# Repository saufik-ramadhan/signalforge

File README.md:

# signalforge
Swiss Army for Hackers

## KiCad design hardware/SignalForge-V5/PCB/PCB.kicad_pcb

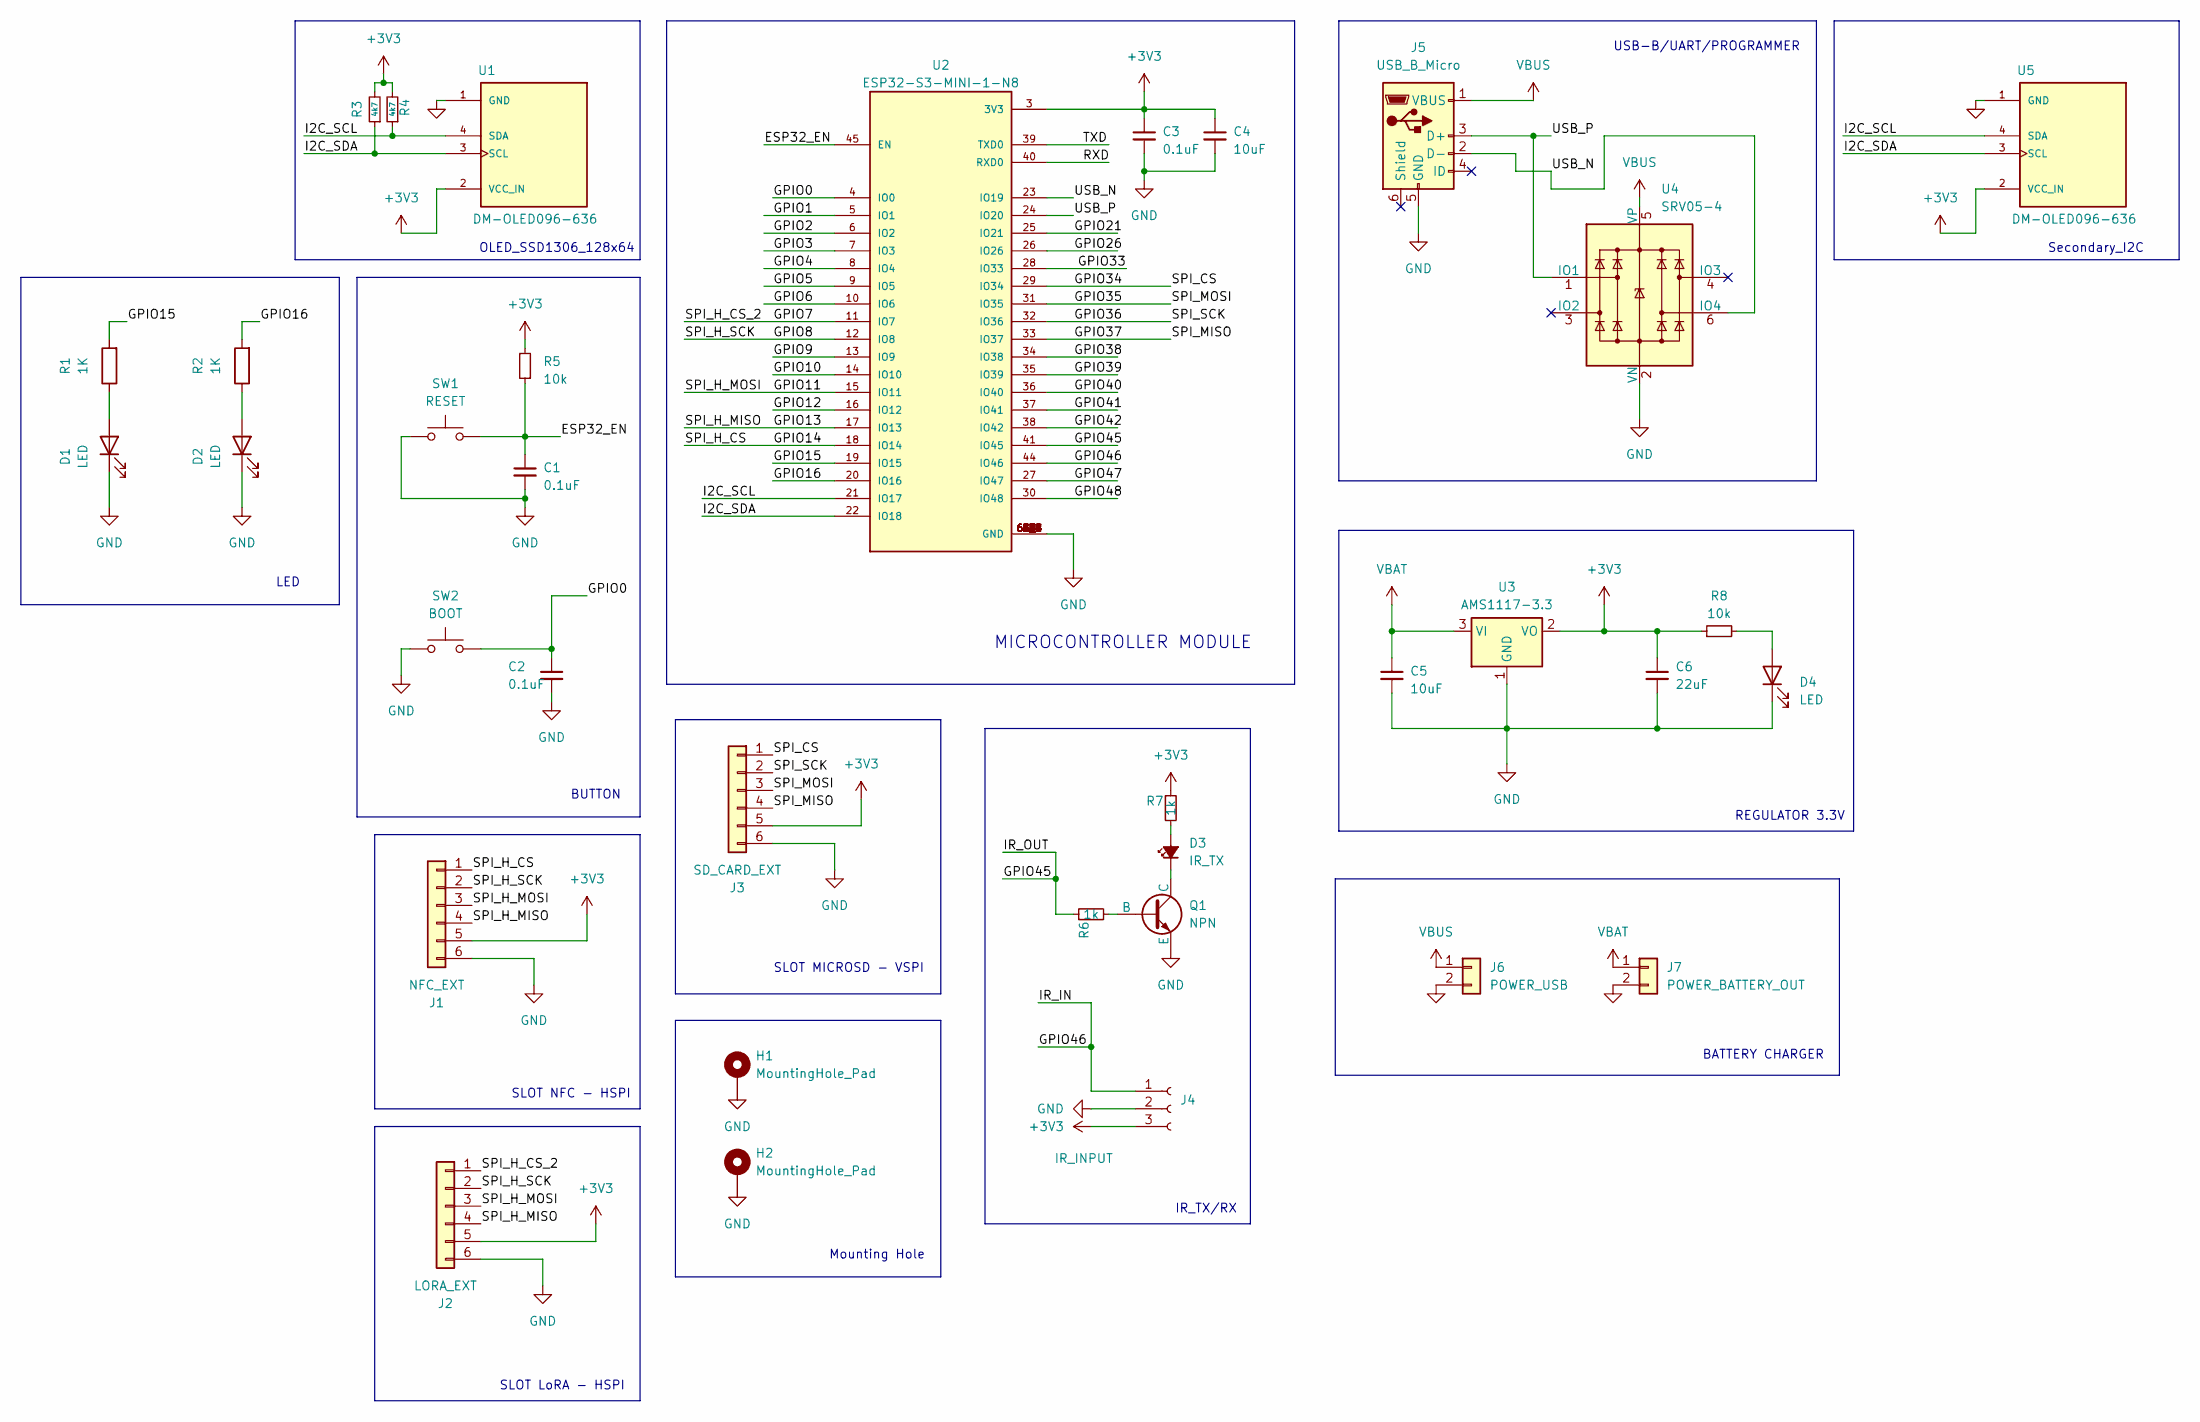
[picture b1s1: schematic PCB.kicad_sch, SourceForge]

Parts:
C1, C2, C3: 0.1uF; C_0603_1608Metric
C4, C5: 10uF; C_0603_1608Metric
C6: 22uF; C_0603_1608Metric
D1, D2, D4: LED; LED_0603_1608Metric
D3: IR_TX; PinSocket_1x02_P2.54mm_Vertical
H1, H2: MountingHole_Pad; MountingHole_3.2mm_M3_DIN965_Pad
J1: NFC_EXT; PinSocket_1x06_P2.54mm_Vertical
J2: LORA_EXT; PinSocket_1x06_P2.54mm_Vertical
J3: SD_CARD_EXT; PinSocket_1x06_P2.54mm_Vertical
J4: IR_INPUT; PinSocket_1x03_P2.54mm_Vertical
J5: USB_B_Micro; PinSocket_1x05_P2.54mm_Vertical
J6: POWER_USB; PinSocket_1x02_P2.54mm_Vertical
J7: POWER_BATTERY_OUT; PinSocket_1x02_P2.54mm_Vertical
Q1: NPN; SOT-23_Handsoldering
R1, R2: 1K; R_0603_1608Metric
R3, R4: 4k7; R_0603_1608Metric
R5, R8: 10k; R_0603_1608Metric
R6, R7: 1k; R_0603_1608Metric
SW1: RESET; SW_Push_1P1T_NO_CK_KSC6xxJ
SW2: BOOT; SW_Push_1P1T_NO_CK_KSC6xxJ
U1, U5: DM-OLED096-636; PinSocket_1x04_P2.54mm_Vertical; PARTREV 2018-09-10
U2: ESP32-S3-MINI-1-N8; XCVR_ESP32-S3-MINI-1-N8; PARTREV v0.6
U3: AMS1117-3.3; SOT-223-3_TabPin2
U4: SRV05-4; SOT-23-6

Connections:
+3V3: C3.1, C4.1, C6.1, J1.5, J2.5, J3.5, J4.3, R3.2, R4.2, R5.2, R7.1, R8.1, U1.2 (VCC_IN), U2.3 (3V3), U3.2 (VO), U5.2 (VCC_IN)
/ESP32_EN: C1.1, R5.1, SW1.2, U2.45 (EN)
/GPIO0: C2.1, SW2.2, U2.4 (IO0)
/GPIO1: U2.5 (IO1)
/GPIO2: U2.6 (IO2)
/GPIO3: U2.7 (IO3)
/GPIO4: U2.8 (IO4)
/GPIO5: U2.9 (IO5)
/GPIO6: U2.10 (IO6)
/GPIO7: J2.1, U2.11 (IO7)
/GPIO8: J1.2, J2.2, U2.12 (IO8)
/GPIO9: U2.13 (IO9)
/GPIO10: U2.14 (IO10)
/GPIO11: J1.3, J2.3, U2.15 (IO11)
/GPIO12: U2.16 (IO12)
/GPIO13: J1.4, J2.4, U2.17 (IO13)
/GPIO14: J1.1, U2.18 (IO14)
/GPIO15: R1.2, U2.19 (IO15)
/GPIO16: R2.2, U2.20 (IO16)
/GPIO21: U2.25 (IO21)
/GPIO26: U2.26 (IO26)
/GPIO33: U2.28 (IO33)
/GPIO34: J3.1, U2.29 (IO34)
/GPIO35: J3.3, U2.31 (IO35)
/GPIO36: J3.2, U2.32 (IO36)
/GPIO37: J3.4, U2.33 (IO37)
/GPIO38: U2.34 (IO38)
/GPIO39: U2.35 (IO39)
/GPIO40: U2.36 (IO40)
/GPIO41: U2.37 (IO41)
/GPIO42: U2.38 (IO42)
/GPIO45: R6.1, U2.41 (IO45)
/GPIO46: J4.1, U2.44 (IO46)
/GPIO47: U2.27 (IO47)
/GPIO48: U2.30 (IO48)
/I2C_SCL: R4.1, U1.4 (SDA), U2.21 (IO17), U5.4 (SDA)
/I2C_SDA: R3.1, U1.3 (SCL), U2.22 (IO18), U5.3 (SCL)
/RXD: U2.40 (RXD0)
/TXD: U2.39 (TXD0)
/USB_N: J5.2 (D-), U2.23 (IO19), U4.6 (IO4)
/USB_P: J5.3 (D+), U2.24 (IO20), U4.1 (IO1)
GND: C1.2, C2.2, C3.2, C4.2, C5.2, C6.2, D1.1 (K), D2.1 (K), D4.1 (K), H1.1, H2.1, J1.6, J2.6, J3.6, J4.2, J5.5 (GND), J6.2, J7.2, Q1.3 (E), SW1.1, SW2.1, U1.1 (GND), U2.1 (GND), U2.2 (GND), U2.42 (GND), U2.43 (GND), U2.46 (GND), U2.47 (GND), U2.48 (GND), U2.49 (GND), U2.50 (GND), U2.51 (GND), U2.52 (GND), U2.53 (GND), U2.54 (GND), U2.55 (GND), U2.56 (GND), U2.57 (GND), U2.58 (GND), U2.59 (GND), U2.60 (GND), U2.61 (GND), U2.61_1 (GND), U2.61_2 (GND), U2.61_3 (GND), U2.61_4 (GND), U2.61_5 (GND), U2.61_6 (GND), U2.61_7 (GND), U2.61_8 (GND), U2.62 (GND), U2.63 (GND), U2.64 (GND), U2.65 (GND), U3.1 (GND), U4.2 (VN), U5.1 (GND)
unnamed: D1.2 (A), R1.1
unnamed: D2.2 (A), R2.1
unnamed: D3.2 (A), R7.2
unnamed: D3.1 (K), Q1.1 (C)
unnamed: D4.2 (A), R8.2
unnamed: Q1.2 (B), R6.2
VBAT: C5.1, J7.1, U3.3 (VI)
VBUS: J5.1 (VBUS), J6.1, U4.5 (VP)

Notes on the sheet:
USB-B/UART/PROGRAMMER
OLED_SSD1306_128x64
Mounting Hole
LED
SLOT NFC - HSPI
REGULATOR 3.3V
SLOT LoRA - HSPI
Secondary_I2C
BATTERY CHARGER
BUTTON
MICROCONTROLLER MODULE
IR_TX/RX
SLOT MICROSD - VSPI

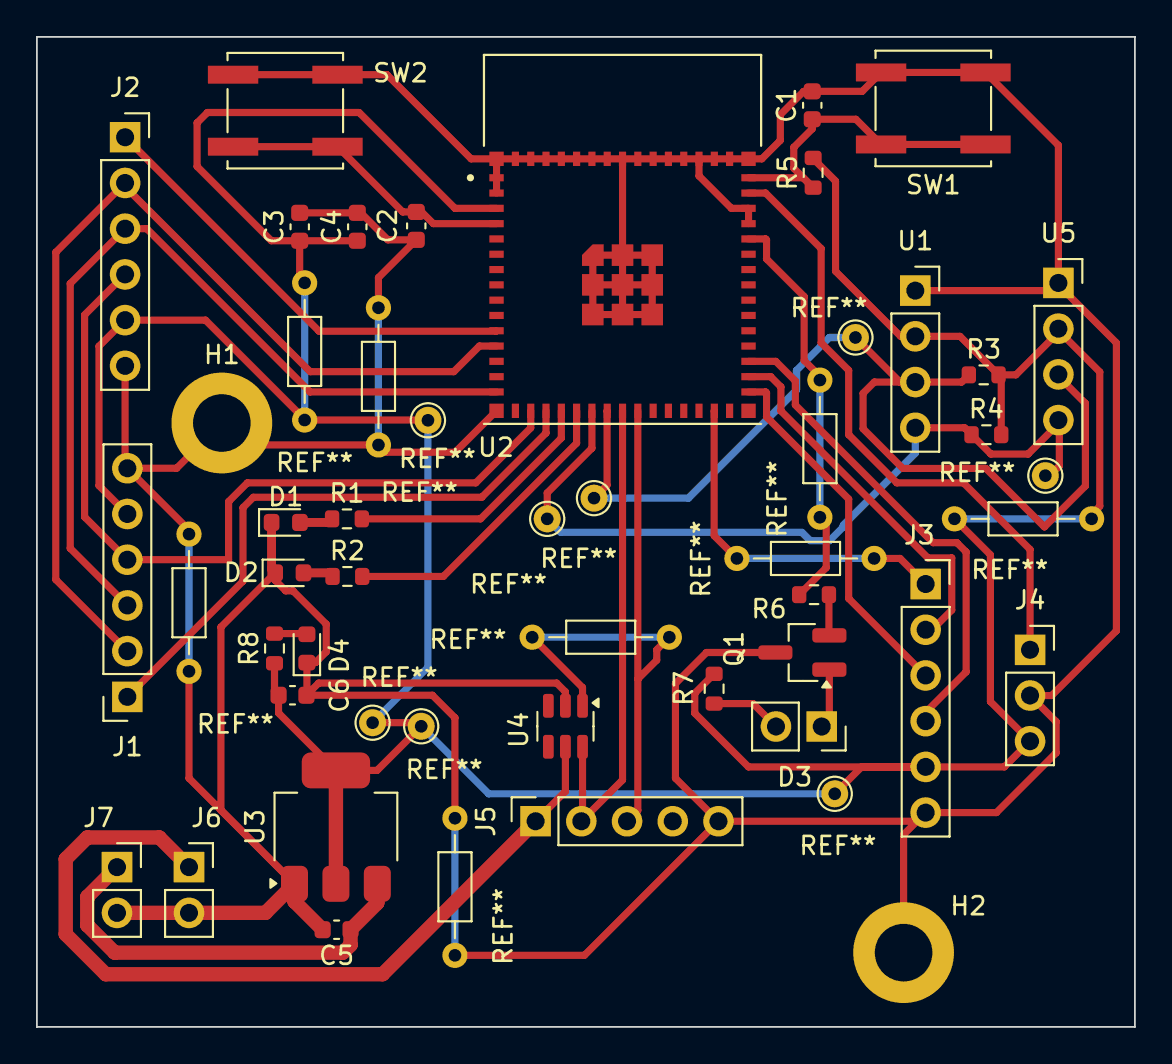
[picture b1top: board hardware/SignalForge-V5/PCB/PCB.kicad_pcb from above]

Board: 2 copper layers, 61.0 x 55.0 mm, 35 parts (0 on the bottom side), 29 nets.

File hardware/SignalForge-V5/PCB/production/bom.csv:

Designator,Footprint,Quantity,Value,LCSC Part #
"C1, C2, C3",0603,3,0.1uF,
"C4, C5",0603,2,10uF,
C6,0603,1,22uF,
"D1, D2, D4",0603,3,LED,
D3,PinSocket_1x02_P2.54mm_Vertical,1,IR_TX,
J1,PinSocket_1x06_P2.54mm_Vertical,1,NFC_EXT,
J2,PinSocket_1x06_P2.54mm_Vertical,1,LORA_EXT,
J3,PinSocket_1x06_P2.54mm_Vertical,1,SD_CARD_EXT,
J4,PinSocket_1x03_P2.54mm_Vertical,1,IR_INPUT,
J5,PinSocket_1x05_P2.54mm_Vertical,1,USB_B_Micro,
J6,PinSocket_1x02_P2.54mm_Vertical,1,POWER_USB,
J7,PinSocket_1x02_P2.54mm_Vertical,1,POWER_BATTERY_OUT,
Q1,SOT-23_Handsoldering,1,NPN,
"R1, R2, R6, R7",0603,4,1K,
"R3, R4",0603,2,4k7,
"R5, R8",0603,2,10k,
SW1,SW_Push_1P1T_NO_CK_KSC6xxJ,1,RESET,
SW2,SW_Push_1P1T_NO_CK_KSC6xxJ,1,BOOT,
"U1, U5",PinSocket_1x04_P2.54mm_Vertical,2,DM-OLED096-636,
U2,XCVR_ESP32-S3-MINI-1-N8,1,ESP32-S3-MINI-1-N8,
U3,SOT-223-3_TabPin2,1,AMS1117-3.3,
U4,SOT-23-6,1,SRV05-4,

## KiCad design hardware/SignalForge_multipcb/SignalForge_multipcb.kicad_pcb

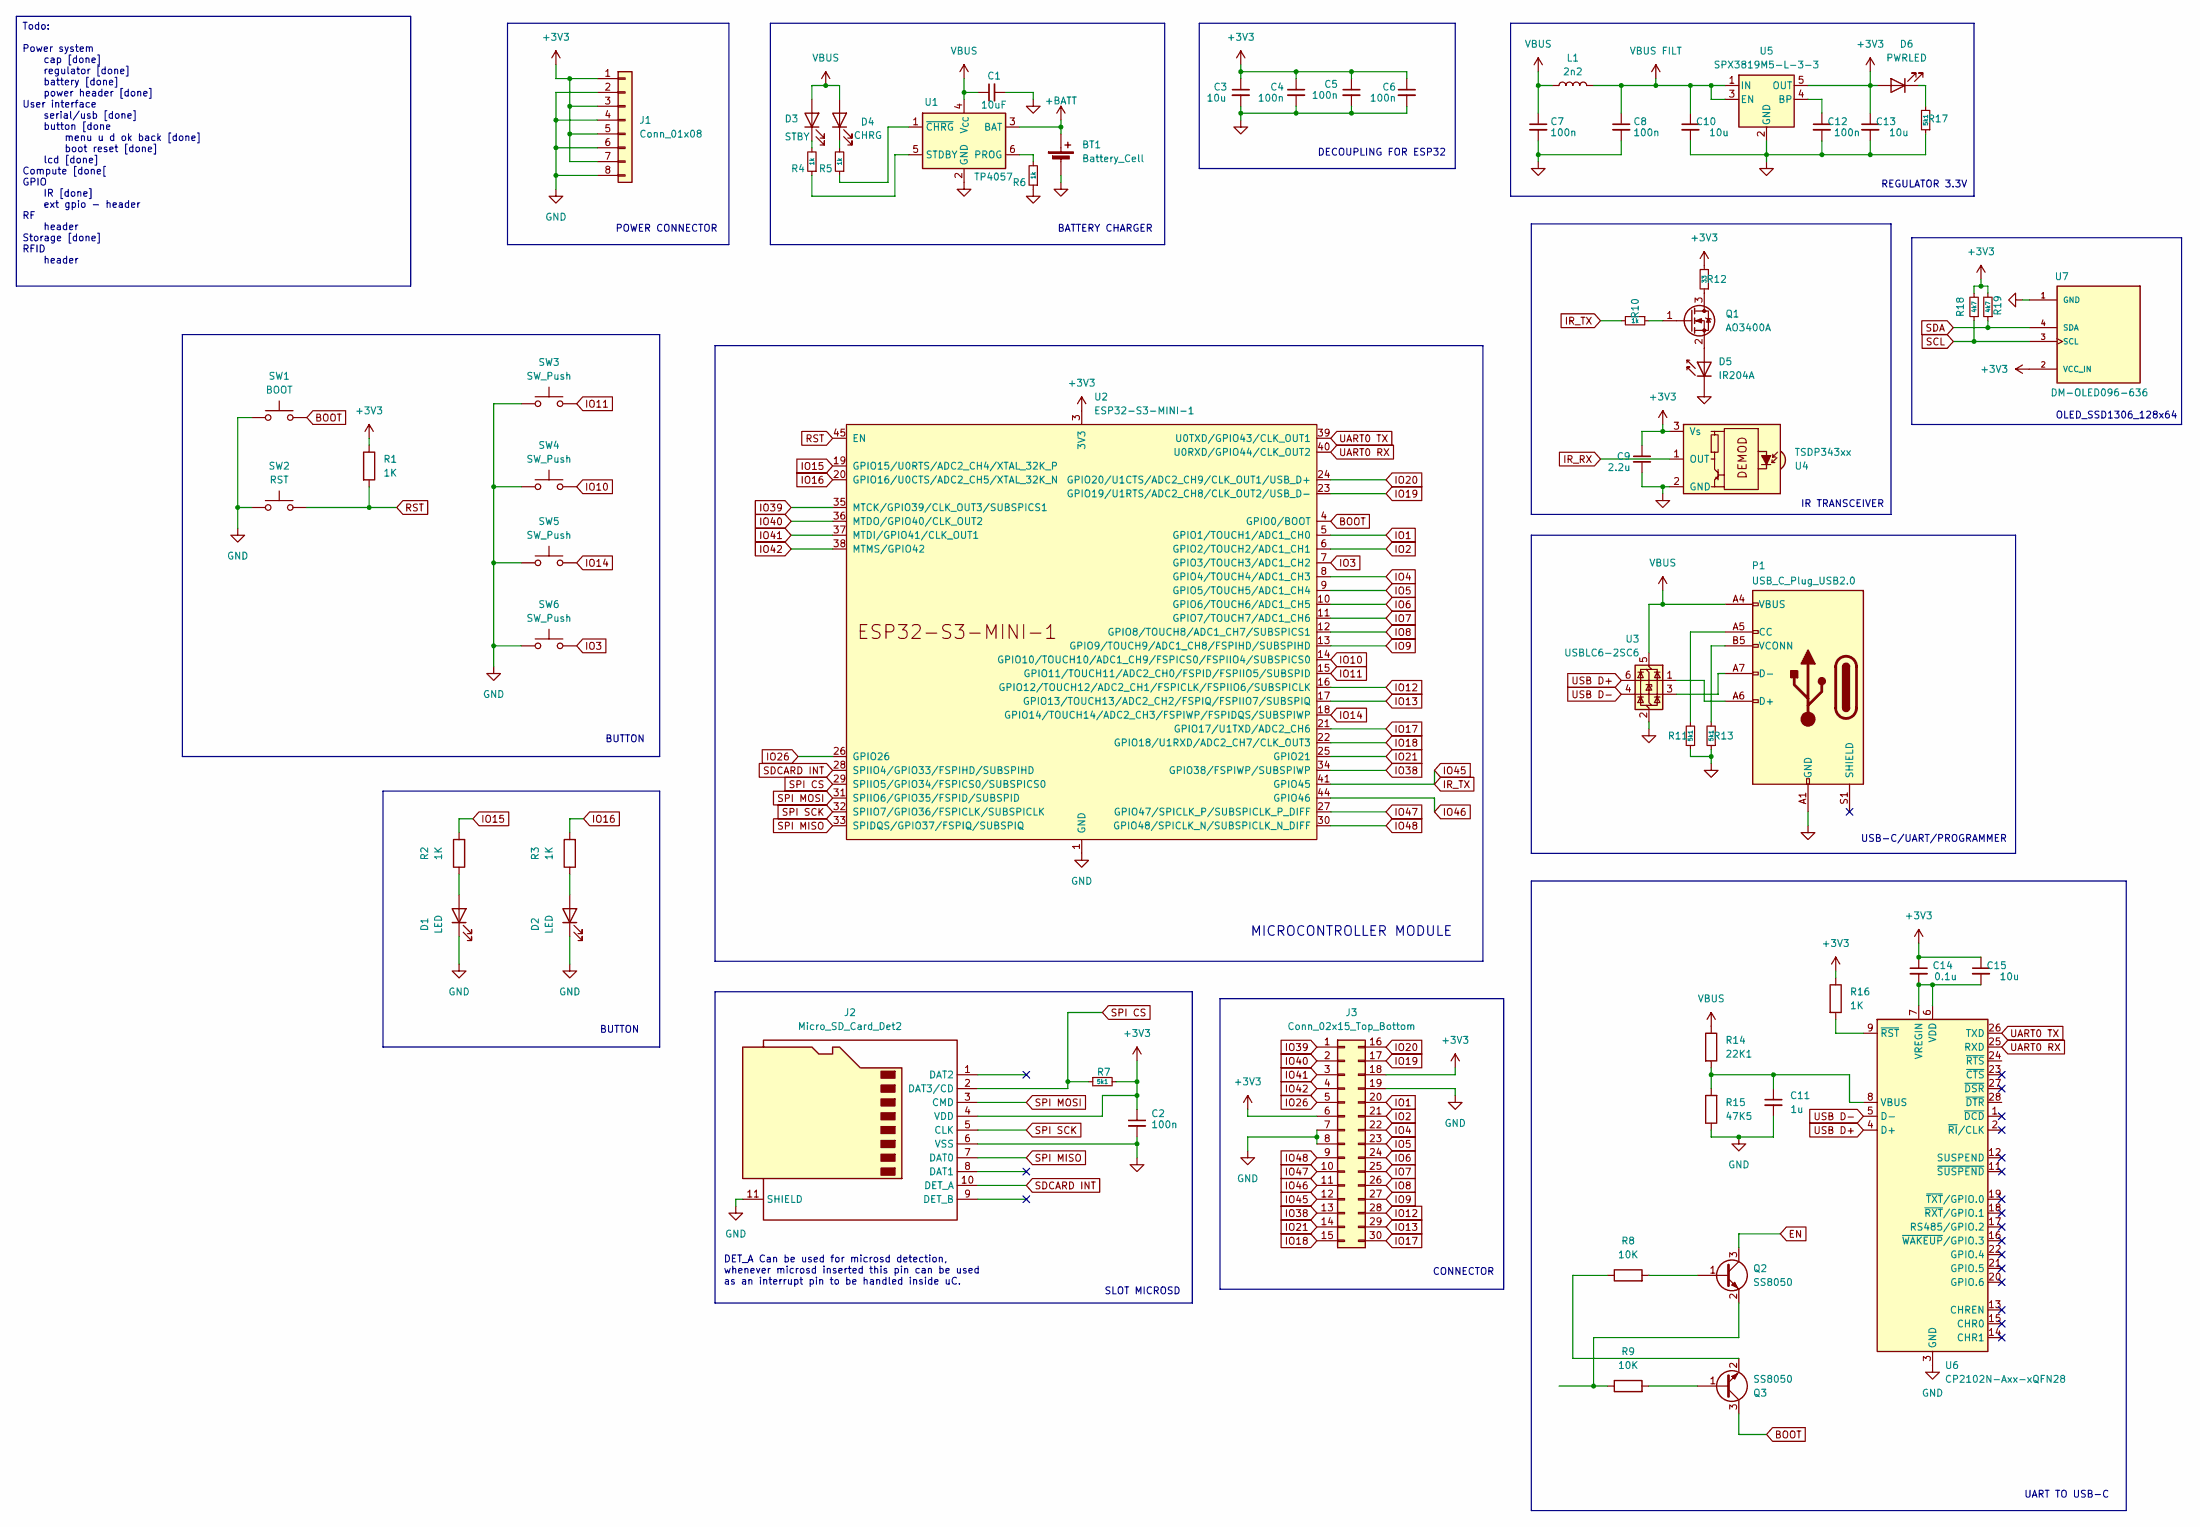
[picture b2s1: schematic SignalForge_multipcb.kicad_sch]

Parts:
BT1: Battery_Cell; SW_PUSH_6mm
C1: 10uF; C_0402_1005Metric
C2, C4, C5, C6, C7, C8, C12: 100n; C_0402_1005Metric
C3, C10, C13, C15: 10u; R_0402_1005Metric_Pad0.72x0.64mm_HandSolder
C9: 2.2u; C_0402_1005Metric
C11: 1u; C_0402_1005Metric
C14: 0.1u; C_0402_1005Metric
D1, D2: LED; LED_D3.0mm_IRBlack
D3: STBY; LED_D3.0mm_IRBlack
D4: CHRG; LED_D3.0mm_IRBlack
D5: IR204A; LED_D3.0mm_IRBlack
D6: PWRLED; LED_D3.0mm_IRBlack
J1: Conn_01x08; PinHeader_1x08_P2.54mm_Vertical
J2: Micro_SD_Card_Det2; microSD_HC_Hirose_DM3BT-DSF-PEJS
J3: Conn_02x15_Top_Bottom; PinHeader_2x15_P2.54mm_Vertical
L1: 2n2; L_0603_1608Metric
P1: USB_C_Plug_USB2.0; USB_C_Receptacle_GCT_USB4105-xx-A_16P_TopMnt_Horizontal
Q1: AO3400A; TO-247-3_Vertical
Q2, Q3: SS8050; TO-247-3_Vertical
R1, R2, R3, R16: 1K; R_1206_3216Metric
R4, R5, R6, R10: 1k; R_1206_3216Metric
R7, R11, R13, R17: 5k1; R_1206_3216Metric
R8, R9: 10K; R_1206_3216Metric
R12: 33; R_1206_3216Metric
R14: 22K1; R_1206_3216Metric
R15: 47K5; R_1206_3216Metric
R18, R19: 4k7; R_1206_3216Metric
SW1: BOOT; SW_SPST_Omron_B3FS-105xP
SW2: RST; SW_SPST_Omron_B3FS-105xP
SW3, SW4, SW5, SW6: SW_Push; SW_SPST_Omron_B3FS-105xP
U1: TP4057; TSOT-23-6
U2: ESP32-S3-MINI-1
U3: USBLC6-2SC6; SOT-23-6
U4: TSDP343xx; Vishay_MOLD-3Pin
U5: SPX3819M5-L-3-3; SOT-23-5
U6: CP2102N-Axx-xQFN28; QFN-28-1EP_5x5mm_P0.5mm_EP3.35x3.35mm
U7: DM-OLED096-636; PinSocket_1x04_P2.54mm_Vertical; PARTREV 2018-09-10

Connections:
+3V3: C2.1, C3.1, C4.1, C5.1, C6.1, C9.1, C13.1, C14.1, C15.1, D6.2 (A), J1.1, J1.3, J1.5, J1.7, J2.4 (VDD), J3.6, J3.18, R1.1, R7.2, R12.2, R16.1, R18.2, R19.2, U2.3 (3V3), U4.3 (Vs), U5.5 (OUT), U7.2 (VCC_IN)
+BATT: BT1.1 (+), U1.3 (BAT)
BOOT: Q3.3 (C), SW1.2, U2.4 (GPIO0/BOOT)
EN: Q2.3 (C)
GND: BT1.2 (-), C1.2, C2.2, C3.2, C4.2, C5.2, C6.2, C7.2, C8.2, C9.2, C10.2, C11.2, C12.2, C13.2, D1.1 (K), D2.1 (K), D5.1 (K), J1.2, J1.4, J1.6, J1.8, J2.6 (VSS), J2.11 (SHIELD), J3.7, J3.8, J3.19, P1.A1 (GND), P1.A12 (GND), P1.B1 (GND), P1.B12 (GND), R6.1, R11.1, R13.1, R15.1, R17.1, SW1.1, SW2.1, SW3.1, SW4.1, SW5.1, SW6.1, U1.2 (GND), U2.1 (GND), U2.2 (GND), U2.42 (GND), U2.43 (GND), U2.46 (GND), U2.47 (GND), U2.48 (GND), U2.49 (GND), U2.50 (GND), U2.51 (GND), U2.52 (GND), U2.53 (GND), U2.54 (GND), U2.55 (GND), U2.56 (GND), U2.57 (GND), U2.58 (GND), U2.59 (GND), U2.60 (GND), U2.61 (GND), U2.62 (GND), U2.63 (GND), U2.64 (GND), U2.65 (GND), U3.2 (GND), U4.2 (GND), U5.2 (GND), U6.3 (GND), U6.29 (GND), U7.1 (GND)
IO1: J3.20, U2.5 (GPIO1/TOUCH1/ADC1_CH0)
IO2: J3.21, U2.6 (GPIO2/TOUCH2/ADC1_CH1)
IO3: SW6.2, U2.7 (GPIO3/TOUCH3/ADC1_CH2)
IO4: J3.22, U2.8 (GPIO4/TOUCH4/ADC1_CH3)
IO5: J3.23, U2.9 (GPIO5/TOUCH5/ADC1_CH4)
IO6: J3.24, U2.10 (GPIO6/TOUCH6/ADC1_CH5)
IO7: J3.25, U2.11 (GPIO7/TOUCH7/ADC1_CH6)
IO8: J3.26, U2.12 (GPIO8/TOUCH8/ADC1_CH7/SUBSPICS1)
IO9: J3.27, U2.13 (GPIO9/TOUCH9/ADC1_CH8/FSPIHD/SUBSPIHD)
IO10: SW4.2, U2.14 (GPIO10/TOUCH10/ADC1_CH9/FSPICS0/FSPIIO4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)
IO11: SW3.2, U2.15 (GPIO11/TOUCH11/ADC2_CH0/FSPID/FSPIIO5/S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)
IO12: J3.28, U2.16 (GPIO12/TOUCH12/ADC2_CH1/FSPICLK/FSPIIO6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)
IO13: J3.29, U2.17 (GPIO13/TOUCH13/ADC2_CH2/FSPIQ/FSPIIO7/S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)
IO14: SW5.2, U2.18 (GPIO14/TOUCH14/ADC2_CH3/FSPIWP/FSPIDQS/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)
IO15: R2.2, U2.19 (GPIO15/U0RTS/ADC2_CH4/XTAL_32K_P)
IO16: R3.2, U2.20 (GPIO16/U0CTS/ADC2_CH5/XTAL_32K_N)
IO17: J3.30, U2.21 (GPIO17/U1TXD/ADC2_CH6)
IO18: J3.15, U2.22 (GPIO18/U1RXD/ADC2_CH7/CLK_OUT3)
IO19: J3.17, U2.23 (GPIO19/U1RTS/ADC2_CH8/CLK_OUT2/USB_D-)
IO20: J3.16, U2.24 (GPIO20/U1CTS/ADC2_CH9/CLK_OUT1/USB_D+)
IO21: J3.14, U2.25 (GPIO21)
IO26: J3.5, U2.26 (GPIO26)
IO38: J3.13, U2.34 (GPIO38/FSPIWP/SUBSPIWP)
IO39: J3.1, U2.35 (MTCK/GPIO39/CLK_OUT3/SUBSPICS1)
IO40: J3.2, U2.36 (MTDO/GPIO40/CLK_OUT2)
IO41: J3.3, U2.37 (MTDI/GPIO41/CLK_OUT1)
IO42: J3.4, U2.38 (MTMS/GPIO42)
IO45: J3.12, R10.2, U2.41 (GPIO45)
IO46: J3.11, U2.44 (GPIO46)
IO47: J3.10, U2.27 (GPIO47/SPICLK_P/SUBSPICLK_P_DIFF)
IO48: J3.9, U2.30 (GPIO48/SPICLK_N/SUBSPICLK_N_DIFF)
IR_RX: U4.1 (OUT)
unnamed: D1.2 (A), R2.1
unnamed: D2.2 (A), R3.1
unnamed: D3.1 (K), R4.2
unnamed: D4.1 (K), R5.2
unnamed: D5.2 (A), Q1.2 (S)
unnamed: D6.1 (K), R17.2
unnamed: P1.A5 (CC), R11.2
unnamed: P1.A6 (D+), U3.1 (I/O1)
unnamed: P1.A7 (D-), U3.3 (I/O2)
unnamed: P1.B5 (VCONN), R13.2
unnamed: Q1.3 (D), R12.1
unnamed: Q1.1 (G), R10.1
unnamed: Q2.1 (B), R8.2
unnamed: Q2.2 (E), R9.1
unnamed: Q3.1 (B), R9.2
unnamed: Q3.2 (E), R8.1
unnamed: R6.2, U1.6 (PROG)
unnamed: R4.1, U1.5 (STDBY)
unnamed: R5.1, U1.1 (~CHRG)
unnamed: C12.1, U5.4 (BP)
unnamed: C11.1, R14.2, R15.2, U6.8 (VBUS)
unnamed: C14.2, C15.2, U6.6 (VDD), U6.7 (VREGIN)
unnamed: R16.2, U6.9 (~RST)
RST: R1.2, SW2.2, U2.45 (EN)
SCL: R18.1, U7.3 (SCL)
SDA: R19.1, U7.4 (SDA)
SDCARD INT: J2.10 (DET_A), U2.28 (SPIIO4/GPIO33/FSPIHD/SUBSPIHD)
SPI CS: J2.2 (DAT3/CD), R7.1, U2.29 (SPIIO5/GPIO34/FSPICS0/SUBSPICS0)
SPI MISO: J2.7 (DAT0), U2.33 (SPIDQS/GPIO37/FSPIQ/SUBSPIQ)
SPI MOSI: J2.3 (CMD), U2.31 (SPIIO6/GPIO35/FSPID/SUBSPID)
SPI SCK: J2.5 (CLK), U2.32 (SPIIO7/GPIO36/FSPICLK/SUBSPICLK)
UART0 RX: U2.40 (U0RXD/GPIO44/CLK_OUT2), U6.25 (RXD)
UART0 TX: U2.39 (U0TXD/GPIO43/CLK_OUT1), U6.26 (TXD)
USB D+: U3.6 (I/O1), U6.4 (D+)
USB D-: U3.4 (I/O2), U6.5 (D-)
VBUS: C1.1, C7.1, D3.2 (A), D4.2 (A), L1.1, P1.A4 (VBUS), P1.A9 (VBUS), P1.B4 (VBUS), P1.B9 (VBUS), R14.1, U1.4 (V_{CC}), U3.5 (VBUS)
VBUS FILT: C8.1, C10.1, L1.2, U5.1 (IN), U5.3 (EN)

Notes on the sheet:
Todo: Power system cap [done] regulator [done] battery [done] power header [done] User interface serial/usb [done] button [done menu u d ok back [done] boot reset [done] lcd [done] Compute [done[ GPIO IR [done] ext gpio - header RF header Storage [done] RFID header
POWER CONNECTOR
IR TRANSCEIVER
USB-C/UART/PROGRAMMER
CONNECTOR
BUTTON
UART TO USB-C
MICROCONTROLLER MODULE
BATTERY CHARGER
OLED_SSD1306_128x64
DECOUPLING FOR ESP32
REGULATOR 3.3V
DET_A Can be used for microsd detection, whenever microsd inserted this pin can be used as an interrupt pin to be handled inside uC.
SLOT MICROSD

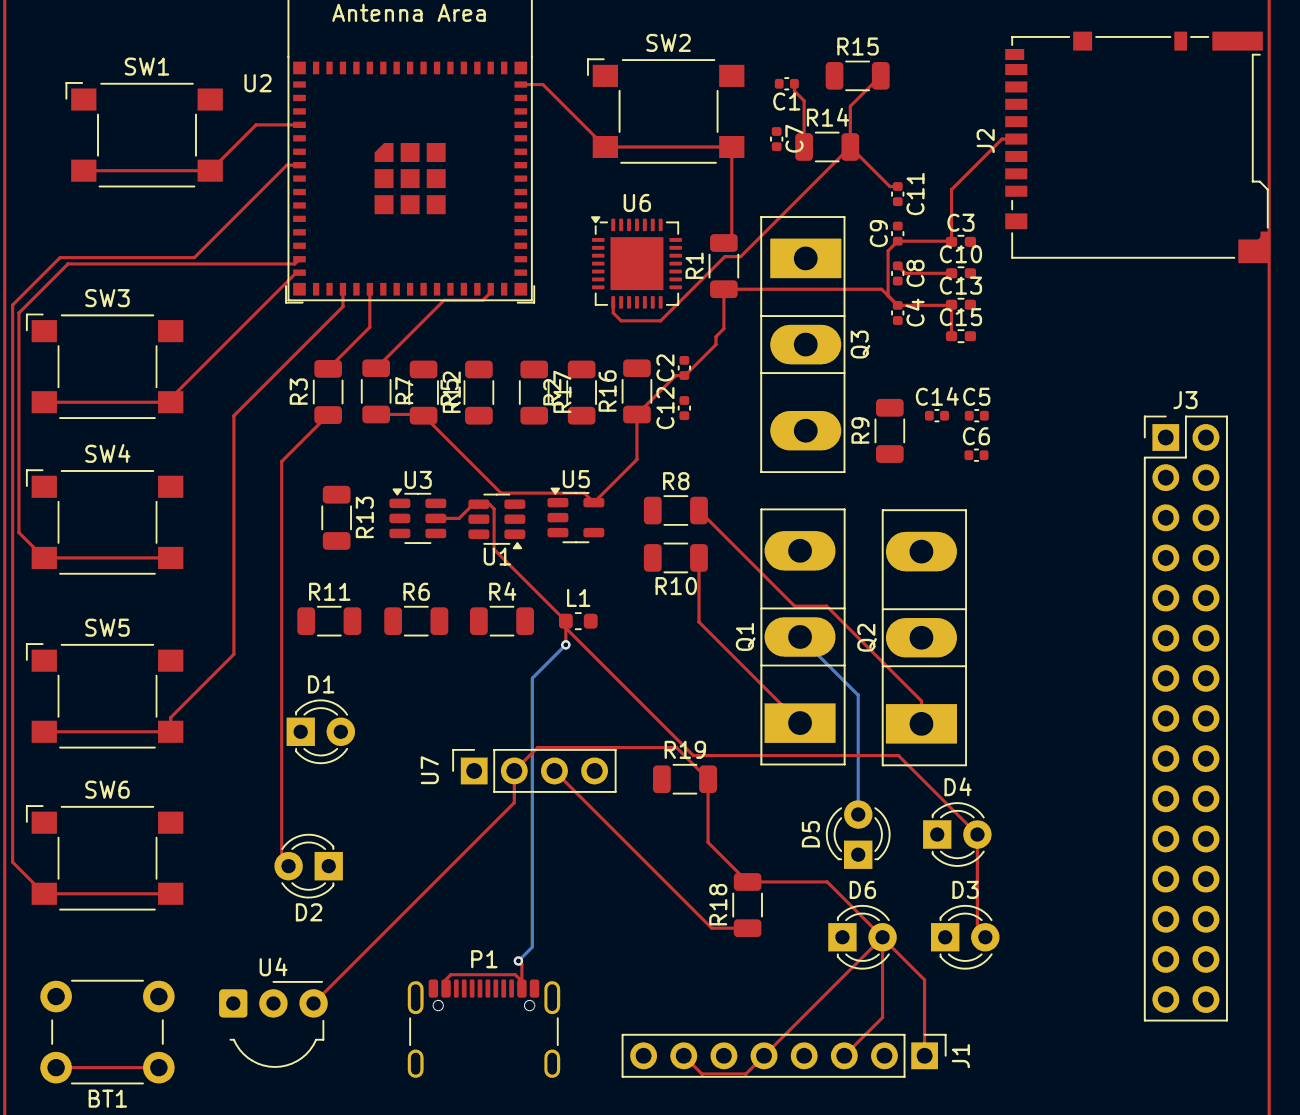
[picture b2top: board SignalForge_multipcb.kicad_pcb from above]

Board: 4 copper layers, 62 parts (0 on the bottom side), 72 nets.

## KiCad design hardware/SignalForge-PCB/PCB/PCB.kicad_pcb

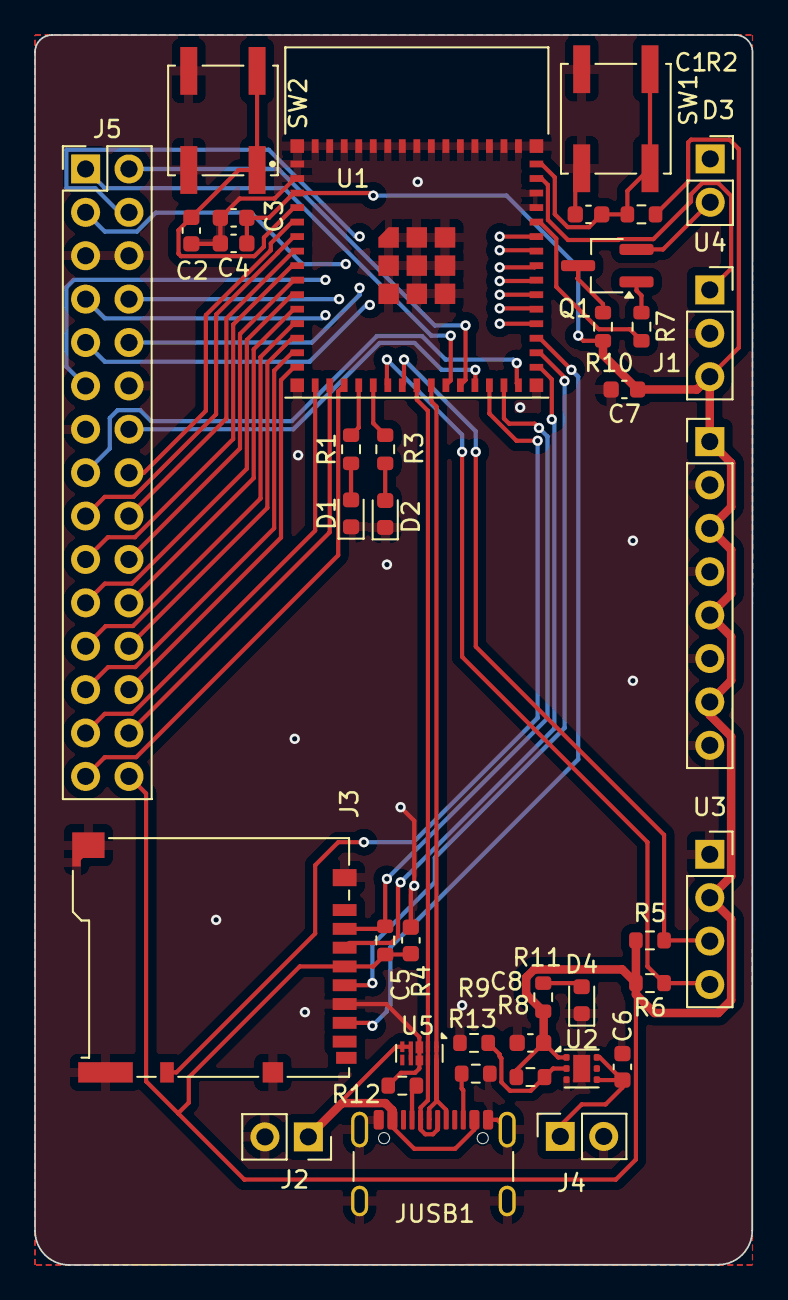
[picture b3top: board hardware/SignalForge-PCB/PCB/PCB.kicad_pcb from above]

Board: 4 copper layers, 42.0 x 72.0 mm, 39 parts (0 on the bottom side), 53 nets.

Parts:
C1, C2, C3: 0.1uF; C_0603_1608Metric
C4, C6, C8: 10uF; C_0603_1608Metric
C5: 100n; C_0603_1608Metric
C7: 2.2u; C_0603_1608Metric
D1, D2, D4: LED; LED_0603_1608Metric
D3: IR204A; PinSocket_1x02_P2.54mm_Vertical
J1: Conn_01x08; PinHeader_1x08_P2.54mm_Vertical
J2, J4: Conn_01x02; PinSocket_1x02_P2.54mm_Vertical
J3: Micro_SD_Card_Det2; microSD_HC_Hirose_DM3BT-DSF-PEJS
J5: Conn_02x15_Top_Bottom; PinHeader_2x15_P2.54mm_Vertical
JUSB1: USB_C_Receptacle_USB2.0; USB_C_Receptacle_GCT_USB4105-xx-A_16P_TopMnt_Horizontal
Q1: AO3400A; TSOT-23_HandSoldering
R1, R3: 1K; R_0603_1608Metric
R2: 10k; R_0603_1608Metric
R4: 5k1; R_0603_1608Metric
R5, R6: 4k7; R_0603_1608Metric
R7: 1k; R_0603_1608Metric
R8: 1M; R_0603_1608Metric
R9: 200k; R_0603_1608Metric
R10: 33; R_0603_1608Metric
R11, R12, R13: 5.1k; R_0603_1608Metric
SW1: RESET; SW_Push_1P1T_NO_CK_KSC6xxJ
SW2: BOOT; SW_Push_1P1T_NO_CK_KSC6xxJ
U1: ESP32-S3-MINI-1-N8; XCVR_ESP32-S3-MINI-1-N8
U2: TLV75801PDRV; WSON-6-1EP_2x2mm_P0.65mm_EP1x1.6mm
U3: DM-OLED096-636; PinSocket_1x04_P2.54mm_Vertical
U4: TSDP343xx; PinSocket_1x03_P2.54mm_Vertical
U5: ESD7104MUTAG; Diodes_UDFN-10_1.0x2.5mm_P0.5mm

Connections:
+3V3: C3.1, C4.1, C5.1, C7.1, C8.1, J1.1, J1.3, J1.5, J1.7, J3.4 (VDD), J5.30, R2.2, R4.2, R5.2, R6.2, R8.2, R10.2, R11.1, U1.3 (3V3), U2.1 (OUT), U3.2 (VCC_IN), U4.3 (Vs)
/ESP32_EN: C1.1, R2.1, SW1.2, U1.45 (EN)
/GPIO0: C2.1, SW2.2, U1.4 (IO0)
/GPIO1: J5.16, U1.5 (IO1)
/GPIO2: J5.17, U1.6 (IO2)
/GPIO3: J5.18, U1.7 (IO3)
/GPIO4: J5.19, U1.8 (IO4)
/GPIO5: J5.20, U1.9 (IO5)
/GPIO6: J5.21, U1.10 (IO6)
/GPIO7: J5.22, U1.11 (IO7)
/GPIO8: J5.23, U1.12 (IO8)
/GPIO9: J5.24, U1.13 (IO9)
/GPIO10: J5.25, U1.14 (IO10)
/GPIO11: J5.26, U1.15 (IO11)
/GPIO12: J5.27, U1.16 (IO12)
/GPIO13: J5.28, U1.17 (IO13)
/GPIO14: J5.29, U1.18 (IO14)
/GPIO15: R1.2, U1.19 (IO15)
/GPIO16: R3.2, U1.20 (IO16)
/GPIO21: J5.1, U1.25 (IO21)
/GPIO26: J5.2, U1.26 (IO26)
/GPIO33: J3.10 (DET_A), U1.28 (IO33)
/GPIO34: J3.2 (DAT3/CD), R4.1, U1.29 (IO34)
/GPIO35: J3.3 (CMD), U1.31 (IO35)
/GPIO36: J3.5 (CLK), U1.32 (IO36)
/GPIO37: J3.7 (DAT0), U1.33 (IO37)
/GPIO38: J5.7, U1.34 (IO38)
/GPIO39: J5.8, U1.35 (IO39)
/GPIO40: J5.9, U1.36 (IO40)
/GPIO41: J5.10, U1.37 (IO41)
/GPIO42: J5.11, U1.38 (IO42)
/GPIO45: R7.2, U1.41 (IO45)
/GPIO46: U1.44 (IO46), U4.1 (OUT)
/GPIO47: J5.14, U1.27 (IO47)
/GPIO48: J5.15, U1.30 (IO48)
/I2C_SCL: R6.1, U1.21 (IO17), U3.4 (SDA)
/I2C_SDA: R5.1, U1.22 (IO18), U3.3 (SCL)
/RXD: J5.4, U1.40 (RXD0)
/TXD: J5.3, U1.39 (TXD0)
/USB_N: JUSB1.A7 (D-), JUSB1.B7 (D-), U1.23 (IO19), U5.2, U5.9 (NC)
/USB_P: JUSB1.A6 (D+), JUSB1.B6 (D+), U1.24 (IO20), U5.1, U5.10 (NC)
GND: C1.2, C2.2, C3.2, C4.2, C5.2, C6.2, C7.2, C8.2, D1.1 (K), D2.1 (K), D3.1 (K), D4.1 (K), J1.2, J1.4, J1.6, J1.8, J2.2, J3.6 (VSS), J3.11 (SHIELD), J4.2, J5.5, J5.6, J5.12, J5.13, JUSB1.A1 (GND), JUSB1.A12 (GND), JUSB1.B1 (GND), JUSB1.B12 (GND), JUSB1.S1 (SHIELD), R9.1, R12.2, R13.2, SW1.1, SW2.1, U1.1 (GND), U1.2 (GND), U1.42 (GND), U1.43 (GND), U1.46 (GND), U1.47 (GND), U1.48 (GND), U1.49 (GND), U1.50 (GND), U1.51 (GND), U1.52 (GND), U1.53 (GND), U1.54 (GND), U1.55 (GND), U1.56 (GND), U1.57 (GND), U1.58 (GND), U1.59 (GND), U1.60 (GND), U1.61 (GND), U1.61_1 (GND), U1.61_2 (GND), U1.61_3 (GND), U1.61_4 (GND), U1.61_5 (GND), U1.61_6 (GND), U1.61_7 (GND), U1.61_8 (GND), U1.62 (GND), U1.63 (GND), U1.64 (GND), U1.65 (GND), U2.3 (GND), U2.7 (GND), U3.1 (GND), U4.2 (GND), U5.3 (VSS), U5.8 (VSS)
unnamed: D1.2 (A), R1.1
unnamed: D2.2 (A), R3.1
unnamed: D3.2 (A), Q1.2 (S)
unnamed: D4.2 (A), R11.2
unnamed: JUSB1.A5 (CC1), R12.1
unnamed: JUSB1.B5 (CC2), R13.1
unnamed: Q1.3 (D), R10.1
unnamed: Q1.1 (G), R7.1
unnamed: R8.1, R9.2, U2.2 (FB)
VBAT: C6.1, J4.1, U2.4 (EN), U2.6 (IN)
VBUS: J2.1, JUSB1.A4 (VBUS), JUSB1.A9 (VBUS), JUSB1.B4 (VBUS), JUSB1.B9 (VBUS), U5.4, U5.5, U5.7 (NC)

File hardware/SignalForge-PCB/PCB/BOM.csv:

"Id";"Designator";"Footprint";"Quantity";"Designation";"Supplier and ref";
1;"SW2";"SW_Push_1P1T_NO_CK_KSC6xxJ";1;"BOOT";;;
2;"SW1";"SW_Push_1P1T_NO_CK_KSC6xxJ";1;"RESET";;;
3;"U5";"Diodes_UDFN-10_1.0x2.5mm_P0.5mm";1;"ESD7104MUTAG";;;
4;"U4";"PinSocket_1x03_P2.54mm_Vertical";1;"TSDP343xx";;;
5;"U3";"PinSocket_1x04_P2.54mm_Vertical";1;"DM-OLED096-636";;;
6;"U2";"WSON-6-1EP_2x2mm_P0.65mm_EP1x1.6mm";1;"TLV75801PDRV";;;
7;"R8";"R_0603_1608Metric";1;"1M";;;
8;"R7";"R_0603_1608Metric";1;"1k";;;
9;"R6,R5";"R_0603_1608Metric";2;"4k7";;;
10;"J5";"PinHeader_2x15_P2.54mm_Vertical";1;"Conn_02x15_Top_Bottom";;;
11;"J2,J4";"PinSocket_1x02_P2.54mm_Vertical";2;"Conn_01x02";;;
12;"D4,D2,D1";"LED_0603_1608Metric";3;"LED";;;
13;"D3";"PinSocket_1x02_P2.54mm_Vertical";1;"IR204A";;;
14;"C2,C3,C1";"C_0603_1608Metric";3;"0.1uF";;;
15;"Q1";"TSOT-23_HandSoldering";1;"AO3400A";;;
16;"R13,R12,R11";"R_0603_1608Metric";3;"5.1k";;;
17;"R4";"R_0603_1608Metric";1;"5k1";;;
18;"R3,R1";"R_0603_1608Metric";2;"1K";;;
19;"R2";"R_0603_1608Metric";1;"10k";;;
20;"C8,C6,C4";"C_0603_1608Metric";3;"10uF";;;
21;"U1";"XCVR_ESP32-S3-MINI-1-N8";1;"ESP32-S3-MINI-1-N8";;;
22;"R10";"R_0603_1608Metric";1;"33";;;
23;"R9";"R_0603_1608Metric";1;"200k";;;
24;"JUSB1";"USB_C_Receptacle_GCT_USB4105-xx-A_16P_TopMnt_Horizontal";1;"USB_C_Receptacle_USB2.0";;;
25;"J1";"PinHeader_1x08_P2.54mm_Vertical";1;"Conn_01x08";;;
26;"C7";"C_0603_1608Metric";1;"2.2u";;;
27;"C5";"C_0603_1608Metric";1;"100n";;;
28;"J3";"microSD_HC_Hirose_DM3BT-DSF-PEJS";1;"Micro_SD_Card_Det2";;;

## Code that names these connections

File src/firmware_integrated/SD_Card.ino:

/*
 * pin 1 - not used          |  Micro SD card     |
 * pin 2 - CS (SS)           |                   /
 * pin 3 - DI (MOSI)         |                  |__
 * pin 4 - VDD (3.3V)        |                    |
 * pin 5 - SCK (SCLK)        | 8 7 6 5 4 3 2 1   /
 * pin 6 - VSS (GND)         | ▄ ▄ ▄ ▄ ▄ ▄ ▄ ▄  /
 * pin 7 - DO (MISO)         | ▀ ▀ █ ▀ █ ▀ ▀ ▀ |
 * pin 8 - not used          |_________________|
 *                             ║ ║ ║ ║ ║ ║ ║ ║
 *                     ╔═══════╝ ║ ║ ║ ║ ║ ║ ╚═════════╗
 *                     ║         ║ ║ ║ ║ ║ ╚══════╗    ║
 *                     ║   ╔═════╝ ║ ║ ║ ╚═════╗  ║    ║
 * Connections for     ║   ║   ╔═══╩═║═║═══╗   ║  ║    ║
 * full-sized          ║   ║   ║   ╔═╝ ║   ║   ║  ║    ║
 * SD card             ║   ║   ║   ║   ║   ║   ║  ║    ║
 * Pin name         |  -  DO  VSS SCK VDD VSS DI CS    -  |
 * SD pin number    |  8   7   6   5   4   3   2   1   9 /
 *                  |                                  █/
 *                  |__▍___▊___█___█___█___█___█___█___/
 *
 * Note:  The SPI pins can be manually configured by using `SPI.begin(sck, miso, mosi, cs).`
 *        Alternatively, you can change the CS pin and use the other default settings by using `SD.begin(cs)`.
 *
 * +--------------+---------+-------+----------+----------+----------+----------+----------+
 * | SPI Pin Name | ESP8266 | ESP32 | ESP32‑S2 | ESP32‑S3 | ESP32‑C3 | ESP32‑C6 | ESP32‑H2 |
 * +==============+=========+=======+==========+==========+==========+==========+==========+
 * | CS (SS)      | GPIO15  | GPIO5 | GPIO34   | GPIO10   | GPIO7    | GPIO18   | GPIO0    |
 * +--------------+---------+-------+----------+----------+----------+----------+----------+
 * | DI (MOSI)    | GPIO13  | GPIO23| GPIO35   | GPIO11   | GPIO6    | GPIO19   | GPIO25   |
 * +--------------+---------+-------+----------+----------+----------+----------+----------+
 * | DO (MISO)    | GPIO12  | GPIO19| GPIO37   | GPIO13   | GPIO5    | GPIO20   | GPIO11   |
 * +--------------+---------+-------+----------+----------+----------+----------+----------+
 * | SCK (SCLK)   | GPIO14  | GPIO18| GPIO36   | GPIO12   | GPIO4    | GPIO21   | GPIO10   |
 * +--------------+---------+-------+----------+----------+----------+----------+----------+
 *
 * For more info see file README.md in this library or on URL:
 * https://github.com/espressif/arduino-esp32/tree/master/libraries/SD
 */

/*
Uncomment and set up if you want to use custom pins for the SPI communication
#define REASSIGN_PINS
int sck = -1;
int miso = -1;
int mosi = -1;
int cs = -1;
*/

void listDir(fs::FS &fs, const char *dirname, uint8_t levels) {
  Serial.printf("Listing directory: %s\n", dirname);

  File root = fs.open(dirname);
  if (!root) {
    Serial.println("Failed to open directory");
    return;
  }
  if (!root.isDirectory()) {
    Serial.println("Not a directory");
    return;
  }

  File file = root.openNextFile();
  while (file) {
    if (file.isDirectory()) {
      Serial.print("  DIR : ");
      Serial.println(file.name());
      if (levels) {
        listDir(fs, file.path(), levels - 1);
      }
    } else {
      Serial.print("  FILE: ");
      Serial.print(file.name());
      Serial.print("  SIZE: ");
      Serial.println(file.size());
    }
    file = root.openNextFile();
  }
}

void createDir(fs::FS &fs, const char *path) {
  Serial.printf("Creating Dir: %s\n", path);
  if (fs.mkdir(path)) {
    Serial.println("Dir created");
  } else {
    Serial.println("mkdir failed");
  }
}

void removeDir(fs::FS &fs, const char *path) {
  Serial.printf("Removing Dir: %s\n", path);
  if (fs.rmdir(path)) {
    Serial.println("Dir removed");
  } else {
    Serial.println("rmdir failed");
  }
}

void readFile(fs::FS &fs, const char *path) {
  Serial.printf("Reading file: %s\n", path);

  File file = fs.open(path);
  if (!file) {
    Serial.println("Failed to open file for reading");
    return;
  }

  Serial.print("Read from file: ");
  while (file.available()) {
    Serial.write(file.read());
  }
  file.close();
}

void writeFile(fs::FS &fs, const char *path, const char *message) {
  Serial.printf("Writing file: %s\n", path);

  File file = fs.open(path, FILE_WRITE);
  if (!file) {
    Serial.println("Failed to open file for writing");
    return;
  }
  if (file.print(message)) {
    Serial.println("File written");
  } else {
    Serial.println("Write failed");
  }
  file.close();
}

void appendFile(fs::FS &fs, const char *path, const char *message) {
  Serial.printf("Appending to file: %s\n", path);

  File file = fs.open(path, FILE_APPEND);
  if (!file) {
    Serial.println("Failed to open file for appending");
    return;
  }
  if (file.print(message)) {
    Serial.println("Message appended");
  } else {
    Serial.println("Append failed");
  }
  file.close();
}

void renameFile(fs::FS &fs, const char *path1, const char *path2) {
  Serial.printf("Renaming file %s to %s\n", path1, path2);
  if (fs.rename(path1, path2)) {
    Serial.println("File renamed");
  } else {
    Serial.println("Rename failed");
  }
}

void deleteFile(fs::FS &fs, const char *path) {
  Serial.printf("Deleting file: %s\n", path);
  if (fs.remove(path)) {
    Serial.println("File deleted");
  } else {
    Serial.println("Delete failed");
  }
}

void testFileIO(fs::FS &fs, const char *path) {
  File file = fs.open(path);
  static uint8_t buf[512];
  size_t len = 0;
  uint32_t start = millis();
  uint32_t end = start;
  if (file) {
    len = file.size();
    size_t flen = len;
    start = millis();
    while (len) {
      size_t toRead = len;
      if (toRead > 512) {
        toRead = 512;
      }
      file.read(buf, toRead);
      len -= toRead;
    }
    end = millis() - start;
    Serial.printf("%u bytes read for %lu ms\n", flen, end);
    file.close();
  } else {
    Serial.println("Failed to open file for reading");
  }

  file = fs.open(path, FILE_WRITE);
  if (!file) {
    Serial.println("Failed to open file for writing");
    return;
  }

  size_t i;
  start = millis();
  for (i = 0; i < 2048; i++) {
    file.write(buf, 512);
  }
  end = millis() - start;
  Serial.printf("%u bytes written for %lu ms\n", 2048 * 512, end);
  file.close();
}

void sdCardInit() {
  if (!SD.begin()) {
    Serial.println("SDCARD <FAILED> Card Mount Failed");
  }
  uint8_t cardType = SD.cardType();
  if (cardType == CARD_NONE) {
    Serial.println("SDCARD <FAILED> No SD card attached");
    return;
  }
  Serial.print("SDCARD <OK> Type: ");
  if (cardType == CARD_MMC) {
    Serial.println("MMC");
  } else if (cardType == CARD_SD) {
    Serial.println("SDSC");
  } else if (cardType == CARD_SDHC) {
    Serial.println("SDHC");
  } else {
    Serial.println("UNKNOWN");
  }
  uint64_t cardSize = SD.cardSize() / (1024 * 1024);
  Serial.printf("SDCARD Size: %lluMB\n", cardSize);
}

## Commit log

2024-10-04 vault backup: 2024-10-04 11:20:55
2024-10-05 upload first presentation
2024-10-08 add proposal (undone)
2024-10-08 adding resource to proposal
2024-10-09 add presentation file
2024-10-09 modify background information
2024-10-09 cleanups
2024-10-09 fix: font size
2024-10-21 add plugins, add kanban
2024-10-21 add todolist
2024-10-27 add references and modify intro
2024-10-27 temp: bab 2
2024-10-27 temp: add more content
2024-10-27 add block diagram
2024-10-27 feat: block-diagram, dokumentasi IR read
2024-10-27 feat: add block diagram on proposal
2024-10-27 add files: new presentation and media
2024-10-27 feat: hw schematic (undone)
2024-10-27 feat: ir emulator undone
2024-11-04 sw: sdcard, camera
2024-11-07 feat: ir, nfc, battery charger
2024-11-07 feat: sw IR Remote based on IRRemote Arduino
2024-11-10 temp: add poc individual sketch
2024-11-10 add: implementation and testing documen and presentation
2024-11-10 add: wifi sniffer code
2024-11-21 feat: oled menu (undone)
2024-11-21 fix: menu child oled, testing IR send-receive with known protocols
2024-11-22 update dokumen
2024-11-22 update skematik
2024-11-22 swap name
2024-11-23 feat: sd card functions
2024-12-01 add new design
2024-12-30 fix: sd card firmware updater
2025-01-01 add new iteration
2025-01-02 add acrilic casing
2025-01-02 fix: pin definition
2025-01-05 fix: firmware udpate
2025-01-05 a lot of stuff
2025-01-05 fix: ngoprek menu
2025-01-05 new casing
2025-01-05 new casing - step
2025-01-05 fix: merge casing
2025-01-05 temp changes
2025-01-05 temp
2025-01-06 binaries
2025-01-06 update documents
2025-01-06 fix: wifitool
2025-01-06 final
2025-01-06 update ppt
2025-01-06 add closing
2025-01-23 new 3d design
2025-01-23 update steps
2025-01-24 update today
2025-01-24 menu
2025-01-29 fixing formatting
